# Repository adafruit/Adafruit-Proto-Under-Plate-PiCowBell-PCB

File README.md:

## Adafruit Proto Under Plate PiCowBell for Pico - Reset Button & STEMMA QT PCB

<a href="http://www.adafruit.com/products/5905"><br/>
Click here to purchase one from the Adafruit shop</a>

PCB files for the Adafruit Proto Under Plate PiCowBell for Pico - Reset Button & STEMMA QT. 

Format is EagleCAD schematic and board layout
* https://www.adafruit.com/product/5905

### Description

The Adafruit Proto Under Plate PiCowBell is intended to be treated like a mini solder-less proto plate to simplify programming and sensor connectivity for your Raspberry Pi Pico board. Reset button? Yes! STEMMA QT / Qwiic connector for fast I2C? Indeed. Plug-and-play so no soldering necessary when used with a Pico H or Pico WH? Here you go!

This board has double sockets already soldered on, you can plug in your Pico board directly in, and get access to a prototyping area underneath as well as a second row of socket pins. The second row means you can connect wires just by poking them into the header, either directly to LEDs or buttons or to jumper to a breadboard. So you don't have to look up or count pins, each socket is nicely labeled. There's also 4 mounting holes for easy attachment to an underplate. 

The dual socket headers we use are 'hollow' - that means you can connect through the back if desired. Specifically, you can use Pico Stacking Headers to plug through to some other device that is expecting Pico pins. Also, in theory, if you soldered pin headers on the 'wrong side' of a Pico, you could plug it up through the bottom.

We recommend picking up a set of little rubber feet to protect your desk if you're not mounting this board to something else.

The Proto Under Plate PiCowBell provides you with the following:

* 2x20 slim socket headers - plug in your Pico and have an extra row of sockets for each pin! 
* Right angle reset button that sticks out the end
* Right angle JST SH connector for I2C / Stemma QT / Qwiic connection. Or can use it for plain GPIO wiring if you don't have any I2C devices to attach. Provides 3V, GND, IO4 (SDA), and IO5 (SCL)
* There is an extra set of 4 breakout holes next to the JST SH if you want more I2C connections or want to re-assign the I2C port.
* 3 hole-connected strips are in the center area. You can cut the traces between the holes, but they're intended to be treated like a mini-mini breadboard
* Every pad on the Pico has a duplicate hole pad next to it for solder-jumpering
* The ground pads have white silkscreen rectangles to easily identify, plus one long ground strip near the reset button
* One long strip of connected holes for 3.3V power
* Gold-plated pads for easy soldering

We do not have I2C pullups on the board, but your Qwiic/QT breakout board or accessory likely already has them onboard. If using the Philhower Arduino core, the Wire peripheral is already set up to use IO4 and IO5. If using CircuitPython or MicroPython, you'll need to let the code know to look at 4+5 for SDA+SCL pins.

### License

Adafruit invests time and resources providing this open source design, please support Adafruit and open-source hardware by purchasing products from [Adafruit](https://www.adafruit.com)!

Designed by Limor Fried/Ladyada for Adafruit Industries.

Creative Commons Attribution/Share-Alike, all text above must be included in any redistribution. 
See license.txt for additional details.

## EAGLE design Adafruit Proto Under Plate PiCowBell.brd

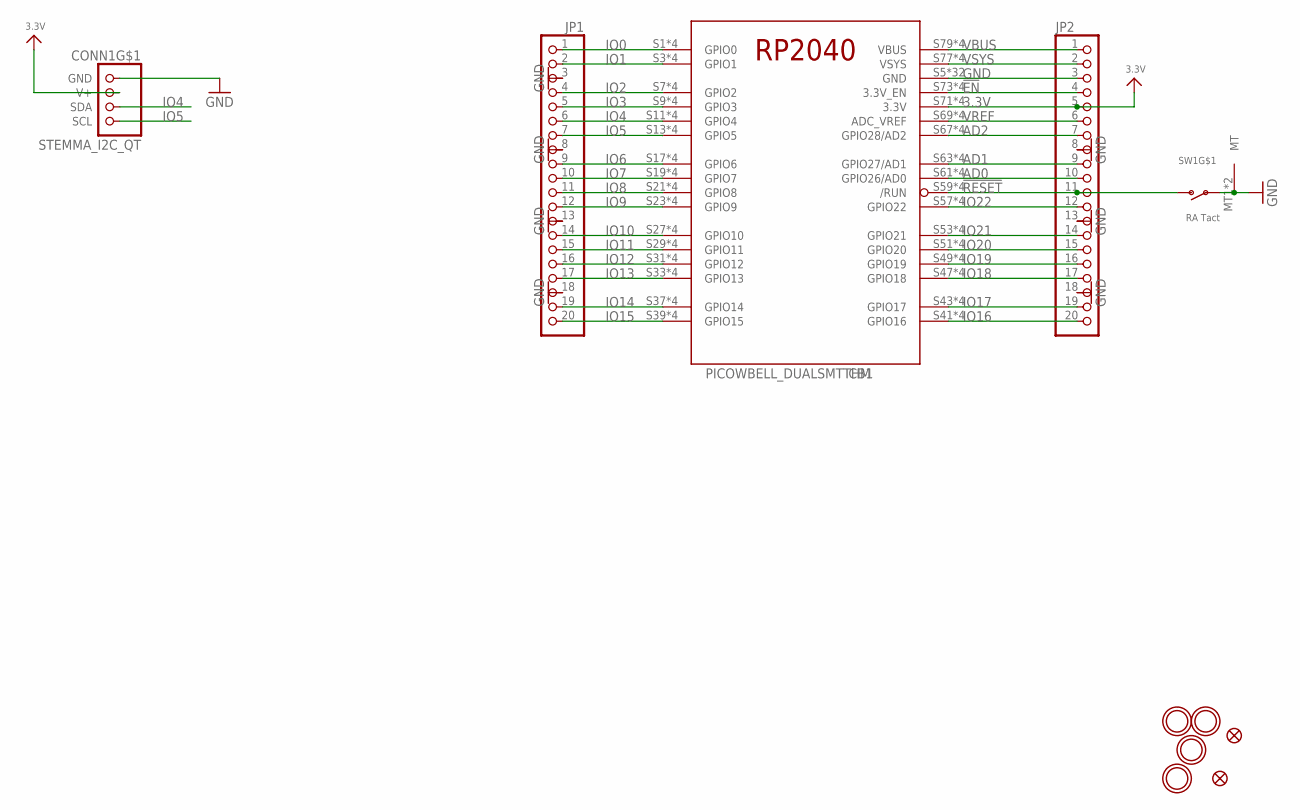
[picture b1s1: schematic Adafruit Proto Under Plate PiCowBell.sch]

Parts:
CB1: PICOWBELL_DUALSMTTHM
CONN1: STEMMA_I2C_QT; JST_SH4
FID1, FID2: FIDUCIAL_1MM
JP1, JP2: HEADER-1X20_70MIL; 1X20_ROUND_70MIL
SW1: RA Tact; SPST_TACTILE_RA
U$5, U$7, U$8, U$9: MOUNTINGHOLE2.5; MOUNTINGHOLE_2.5_PLATED

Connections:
3.3V: CB1.S71 (3.3V), CB1.S72 (3.3V), CB1.T71 (3.3V), CB1.T72 (3.3V), CONN1.2 (V+), JP2.5
!EN: CB1.S73 (3.3V_EN), CB1.S74 (3.3V_EN), CB1.T73 (3.3V_EN), CB1.T74 (3.3V_EN), JP2.4
!RESET: CB1.S59 (/RUN), CB1.S60 (/RUN), CB1.T59 (/RUN), CB1.T60 (/RUN), JP2.11, SW1.2 (S)
AD0: CB1.S61 (GPIO26/AD0), CB1.S62 (GPIO26/AD0), CB1.T61 (GPIO26/AD0), CB1.T62 (GPIO26/AD0), JP2.10
AD1: CB1.S63 (GPIO27/AD1), CB1.S64 (GPIO27/AD1), CB1.T63 (GPIO27/AD1), CB1.T64 (GPIO27/AD1), JP2.9
AD2: CB1.S67 (GPIO28/AD2), CB1.S68 (GPIO28/AD2), CB1.T67 (GPIO28/AD2), CB1.T68 (GPIO28/AD2), JP2.7
GND: CB1.S5 (GND), CB1.S6 (GND), CB1.S15 (GND), CB1.S16 (GND), CB1.S25 (GND), CB1.S26 (GND), CB1.S35 (GND), CB1.S36 (GND), CB1.S45 (GND), CB1.S46 (GND), CB1.S55 (GND), CB1.S56 (GND), CB1.S65 (GND), CB1.S66 (GND), CB1.S75 (GND), CB1.S76 (GND), CB1.T5 (GND), CB1.T6 (GND), CB1.T15 (GND), CB1.T16 (GND), CB1.T25 (GND), CB1.T26 (GND), CB1.T35 (GND), CB1.T36 (GND), CB1.T45 (GND), CB1.T46 (GND), CB1.T55 (GND), CB1.T56 (GND), CB1.T65 (GND), CB1.T66 (GND), CB1.T75 (GND), CB1.T76 (GND), CONN1.1 (GND), JP1.3, JP1.8, JP1.13, JP1.18, JP2.3, JP2.8, JP2.13, JP2.18, SW1.1, SW1.MT1 (MT), SW1.MT2 (MT)
IO0: CB1.S1 (GPIO0), CB1.S2 (GPIO0), CB1.T1 (GPIO0), CB1.T2 (GPIO0), JP1.1
IO1: CB1.S3 (GPIO1), CB1.S4 (GPIO1), CB1.T3 (GPIO1), CB1.T4 (GPIO1), JP1.2
IO2: CB1.S7 (GPIO2), CB1.S8 (GPIO2), CB1.T7 (GPIO2), CB1.T8 (GPIO2), JP1.4
IO3: CB1.S9 (GPIO3), CB1.S10 (GPIO3), CB1.T9 (GPIO3), CB1.T10 (GPIO3), JP1.5
IO4: CB1.S11 (GPIO4), CB1.S12 (GPIO4), CB1.T11 (GPIO4), CB1.T12 (GPIO4), CONN1.3 (SDA), JP1.6
IO5: CB1.S13 (GPIO5), CB1.S14 (GPIO5), CB1.T13 (GPIO5), CB1.T14 (GPIO5), CONN1.4 (SCL), JP1.7
IO6: CB1.S17 (GPIO6), CB1.S18 (GPIO6), CB1.T17 (GPIO6), CB1.T18 (GPIO6), JP1.9
IO7: CB1.S19 (GPIO7), CB1.S20 (GPIO7), CB1.T19 (GPIO7), CB1.T20 (GPIO7), JP1.10
IO8: CB1.S21 (GPIO8), CB1.S22 (GPIO8), CB1.T21 (GPIO8), CB1.T22 (GPIO8), JP1.11
IO9: CB1.S23 (GPIO9), CB1.S24 (GPIO9), CB1.T23 (GPIO9), CB1.T24 (GPIO9), JP1.12
IO10: CB1.S27 (GPIO10), CB1.S28 (GPIO10), CB1.T27 (GPIO10), CB1.T28 (GPIO10), JP1.14
IO11: CB1.S29 (GPIO11), CB1.S30 (GPIO11), CB1.T29 (GPIO11), CB1.T30 (GPIO11), JP1.15
IO12: CB1.S31 (GPIO12), CB1.S32 (GPIO12), CB1.T31 (GPIO12), CB1.T32 (GPIO12), JP1.16
IO13: CB1.S33 (GPIO13), CB1.S34 (GPIO13), CB1.T33 (GPIO13), CB1.T34 (GPIO13), JP1.17
IO14: CB1.S37 (GPIO14), CB1.S38 (GPIO14), CB1.T37 (GPIO14), CB1.T38 (GPIO14), JP1.19
IO15: CB1.S39 (GPIO15), CB1.S40 (GPIO15), CB1.T39 (GPIO15), CB1.T40 (GPIO15), JP1.20
IO16: CB1.S41 (GPIO16), CB1.S42 (GPIO16), CB1.T41 (GPIO16), CB1.T42 (GPIO16), JP2.20
IO17: CB1.S43 (GPIO17), CB1.S44 (GPIO17), CB1.T43 (GPIO17), CB1.T44 (GPIO17), JP2.19
IO18: CB1.S47 (GPIO18), CB1.S48 (GPIO18), CB1.T47 (GPIO18), CB1.T48 (GPIO18), JP2.17
IO19: CB1.S49 (GPIO19), CB1.S50 (GPIO19), CB1.T49 (GPIO19), CB1.T50 (GPIO19), JP2.16
IO20: CB1.S51 (GPIO20), CB1.S52 (GPIO20), CB1.T51 (GPIO20), CB1.T52 (GPIO20), JP2.15
IO21: CB1.S53 (GPIO21), CB1.S54 (GPIO21), CB1.T53 (GPIO21), CB1.T54 (GPIO21), JP2.14
IO22: CB1.S57 (GPIO22), CB1.S58 (GPIO22), CB1.T57 (GPIO22), CB1.T58 (GPIO22), JP2.12
VBUS: CB1.S79 (VBUS), CB1.S80 (VBUS), CB1.T79 (VBUS), CB1.T80 (VBUS), JP2.1
VREF: CB1.S69 (ADC_VREF), CB1.S70 (ADC_VREF), CB1.T69 (ADC_VREF), CB1.T70 (ADC_VREF), JP2.6
VSYS: CB1.S77 (VSYS), CB1.S78 (VSYS), CB1.T77 (VSYS), CB1.T78 (VSYS), JP2.2

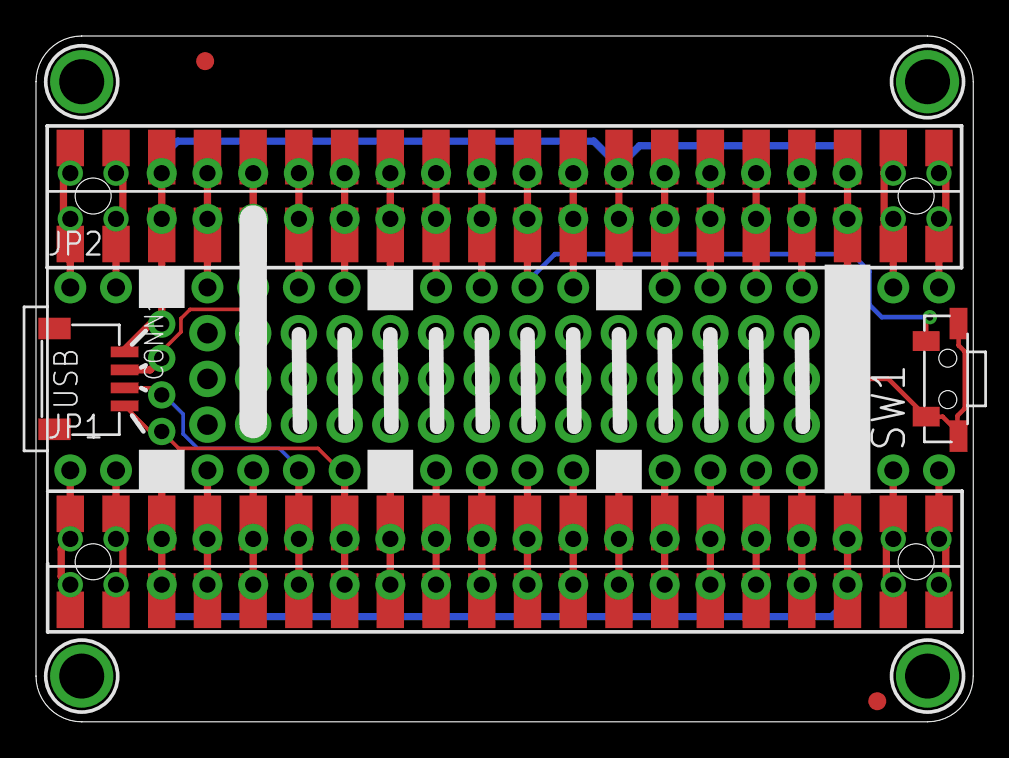
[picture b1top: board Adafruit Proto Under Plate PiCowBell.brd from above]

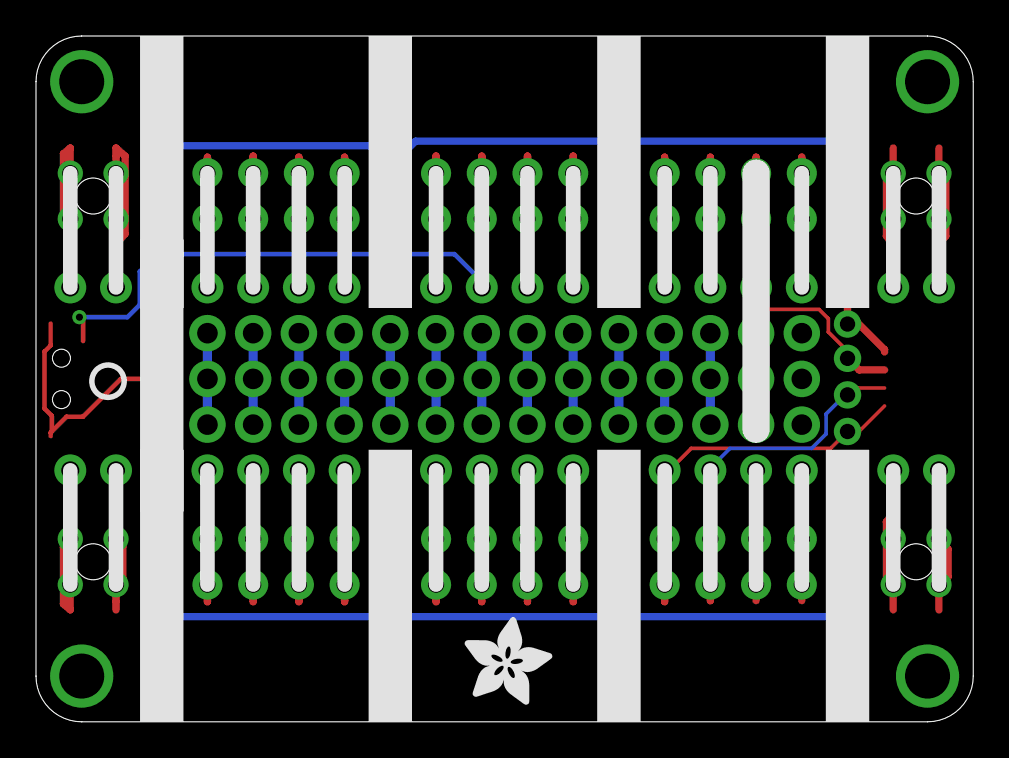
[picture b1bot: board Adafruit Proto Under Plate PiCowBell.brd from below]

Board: 2 copper layers, 52.1 x 38.1 mm, 56 parts (12 on the bottom side), 33 nets.

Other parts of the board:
PLABEL0: PLABEL0
PLABEL1: PLABEL1
PLABEL2: PLABEL2
PLABEL3: PLABEL3
PLABEL4: PLABEL4
PLABEL5: PLABEL5
PLABEL6: PLABEL6
PLABEL7: PLABEL7
PLABEL8: PLABEL8
PLABEL9: PLABEL9
PLABEL10: PLABEL10
PLABEL11: PLABEL11
PLABEL12: PLABEL12
PLABEL13: PLABEL13
PLABEL14: PLABEL14
PLABEL15: PLABEL15
PLABEL16: PLABEL16
PLABEL17: PLABEL17
PLABEL18: PLABEL18
PLABEL19: PLABEL19
PLABEL20: PLABEL20
PLABEL21: PLABEL21
PLABEL22: PLABEL22
PLABEL23: PLABEL23
PLABEL24: PLABEL24
PLABEL25: PLABEL25
PLABEL26: PLABEL26
PLABEL27: PLABEL27
PLABEL28: PLABEL28
PLABEL29: PLABEL29
PLABEL30: PLABEL30
PLABEL31: PLABEL31
PLABEL32: PLABEL32
PLABEL33: PLABEL33
PLABEL34: PLABEL34
PLABEL35: PLABEL35
PLABEL36: PLABEL36
PLABEL37: PLABEL37
PLABEL38: PLABEL38
PLABEL39: PLABEL39
PLABEL40: PLABEL40
PLABEL41: PLABEL41
PLABEL42: PLABEL42
U$6: PCBFEAT-REV-040
U$10: ADAFRUIT_5MM

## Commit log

2024-03-14 cookiecutter

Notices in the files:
parts and their libraries:
microbuilder: This work is placed in the public domain, and may be freely used for commercial and non-commercial work with the following conditions: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
